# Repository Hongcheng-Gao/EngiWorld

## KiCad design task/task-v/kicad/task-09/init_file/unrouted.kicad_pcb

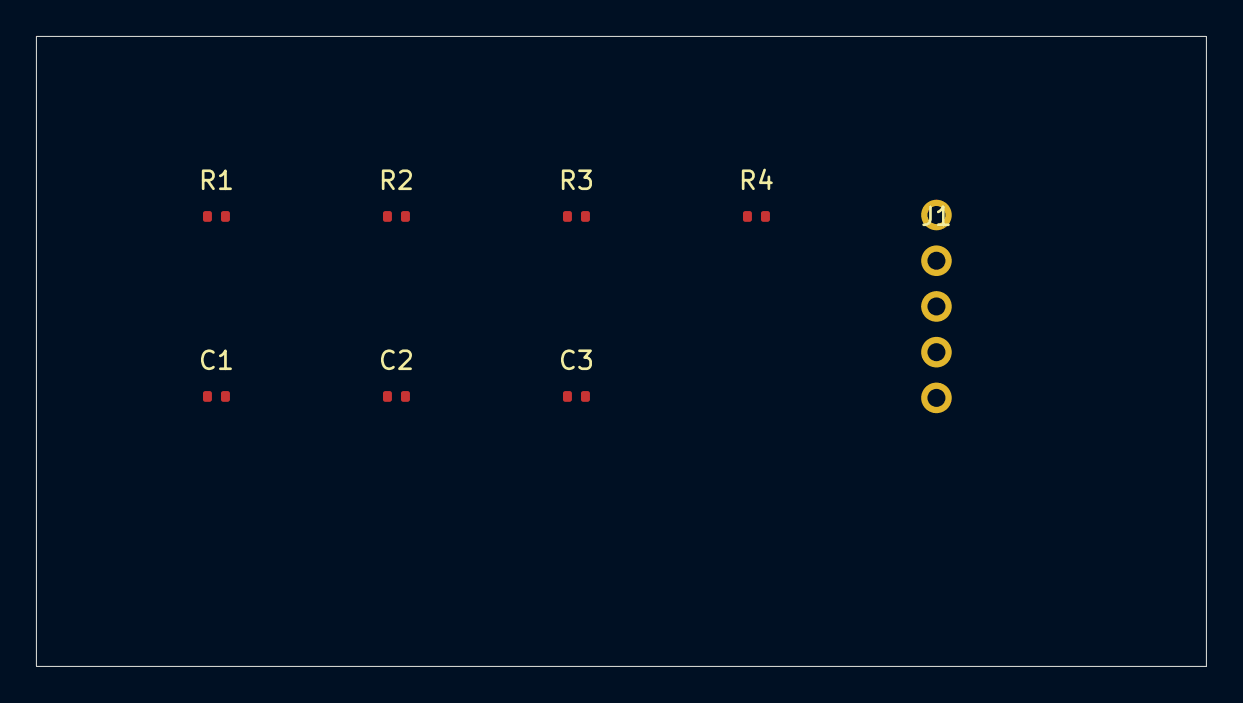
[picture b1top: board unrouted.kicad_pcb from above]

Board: 2 copper layers, 65.0 x 35.0 mm, 8 parts (0 on the bottom side), 5 nets, no tracks yet.

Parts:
C1, C2, C3: 100n; C_0402
J1: CONN_5P; PinHeader_1x05_P2.54mm_Vertical
R1, R2, R3, R4: 10k; R_0402

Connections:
GND: C1.2, C2.2, C3.2, J1.2, R4.2
SIG_A: C2.1, J1.3, R1.2, R2.1
SIG_B: C3.1, J1.4, R2.2, R3.1
SIG_C: J1.5, R3.2, R4.1
VCC: C1.1, J1.1, R1.1

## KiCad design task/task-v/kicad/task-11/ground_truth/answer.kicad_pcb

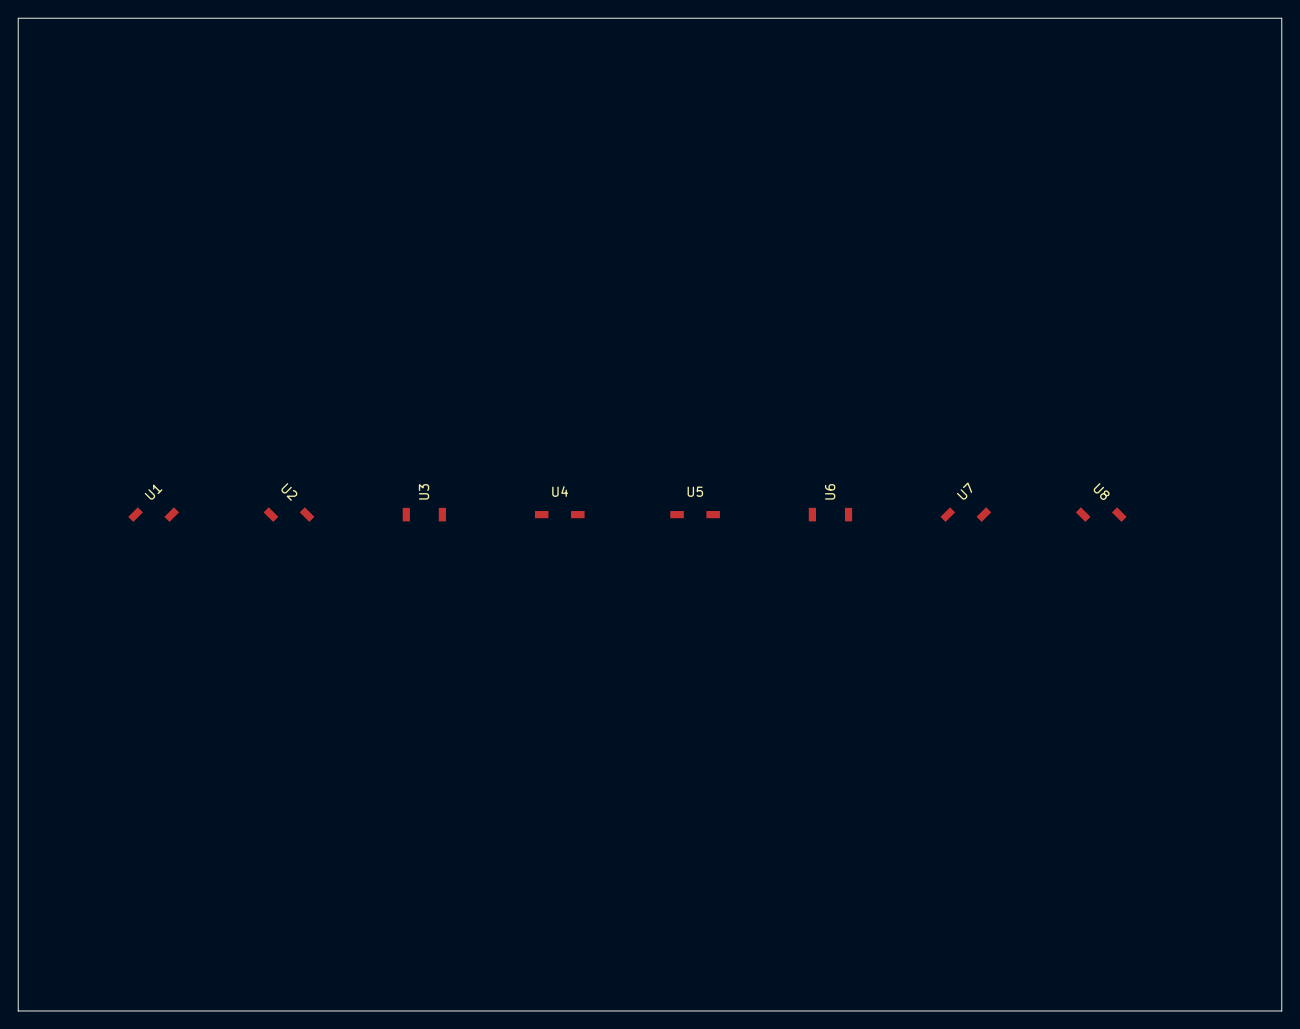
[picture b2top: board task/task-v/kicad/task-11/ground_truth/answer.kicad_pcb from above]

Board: 2 copper layers, 140.0 x 110.0 mm, 8 parts (0 on the bottom side), 7 nets, no tracks yet.

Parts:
U1: ANT; SMA_Amphenol_901-143-8RFX_Vertical
U2: LNA; SOIC-8_3.9x4.9mm_P1.27mm
U3: BPF; SOIC-8_3.9x4.9mm_P1.27mm
U4: MIX; SOIC-8_3.9x4.9mm_P1.27mm
U5: AMP; SOIC-8_3.9x4.9mm_P1.27mm
U6: LPF; SOIC-8_3.9x4.9mm_P1.27mm
U7: ADC; SOIC-16_3.9x9.9mm_P1.27mm
U8: DAQ; SOIC-16_3.9x9.9mm_P1.27mm

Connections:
RF_ADC: U6.2, U7.1
RF_BANDPASS: U2.2, U3.1
RF_DATA: U7.2, U8.1
RF_GAIN: U4.2, U5.1
RF_LOWPASS: U5.2, U6.1
RF_MIX: U3.2, U4.1
RF_PREAMP: U1.2, U2.1

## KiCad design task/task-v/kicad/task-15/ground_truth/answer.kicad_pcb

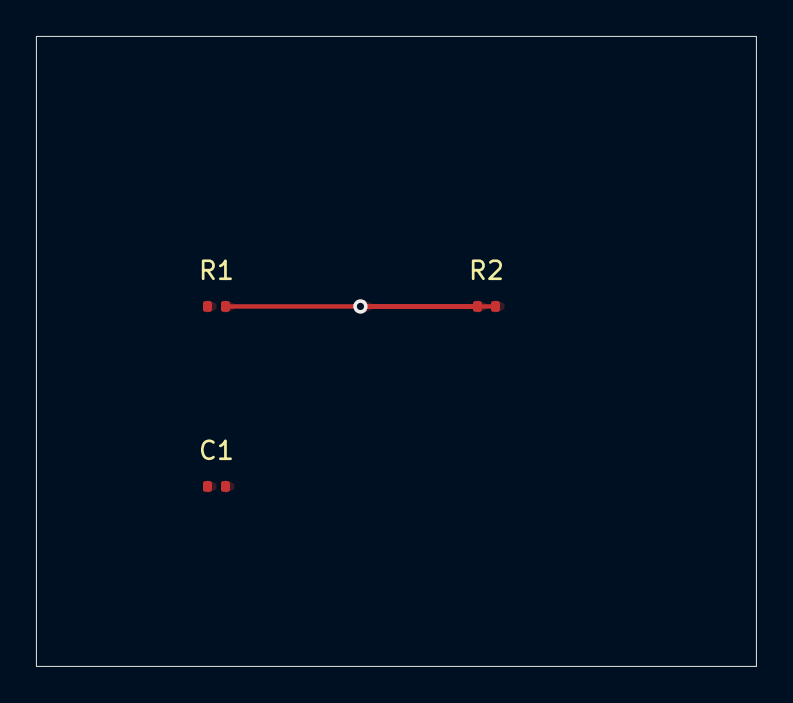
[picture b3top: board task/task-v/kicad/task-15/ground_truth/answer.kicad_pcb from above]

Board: 2 copper layers, 40.0 x 35.0 mm, 3 parts (0 on the bottom side), 2 nets.

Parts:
C1: 100n; C_0402
R1, R2: 10k; R_0402

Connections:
GND: C1.2, R2.2
SIG_A: R1.1, R1.2, R2.1
